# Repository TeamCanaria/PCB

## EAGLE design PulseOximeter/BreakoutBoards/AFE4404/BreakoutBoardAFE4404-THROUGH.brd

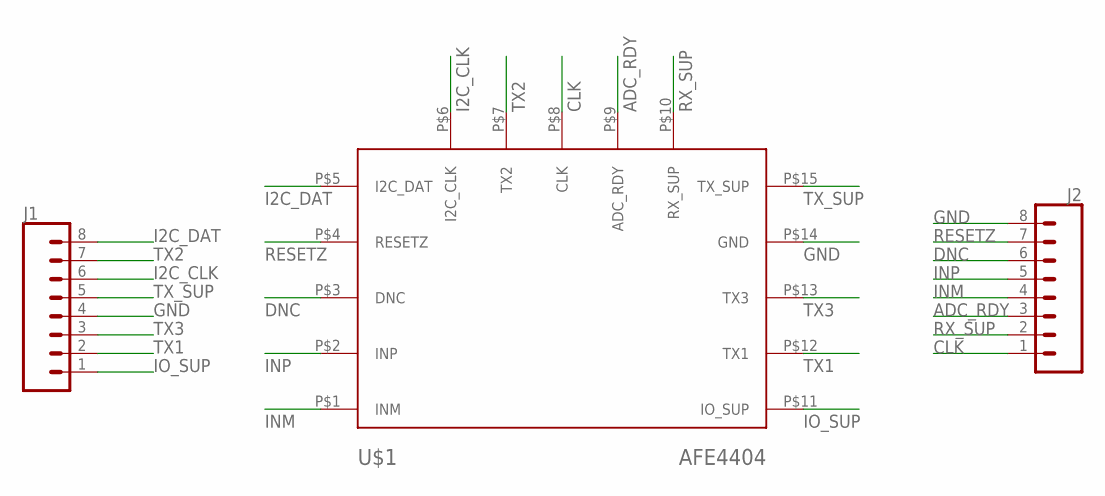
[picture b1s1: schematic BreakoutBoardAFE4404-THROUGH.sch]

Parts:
J1, J2: CONN_08"; 1X08
U$1: AFE4404; AFE4404-THROUGH

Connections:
ADC_RDY: J2.3, U$1.P$9 (ADC_RDY)
CLK: J2.1, U$1.P$8 (CLK)
DNC: J2.6, U$1.P$3 (DNC)
GND: J1.4, J2.8, U$1.P$14 (GND)
I2C_CLK: J1.6, U$1.P$6 (I2C_CLK)
I2C_DAT: J1.8, U$1.P$5 (I2C_DAT)
INM: J2.4, U$1.P$1 (INM)
INP: J2.5, U$1.P$2 (INP)
IO_SUP: J1.1, U$1.P$11 (IO_SUP)
RESETZ: J2.7, U$1.P$4 (RESETZ)
RX_SUP: J2.2, U$1.P$10 (RX_SUP)
TX1: J1.2, U$1.P$12 (TX1)
TX2: J1.7, U$1.P$7 (TX2)
TX3: J1.3, U$1.P$13 (TX3)
TX_SUP: J1.5, U$1.P$15 (TX_SUP)

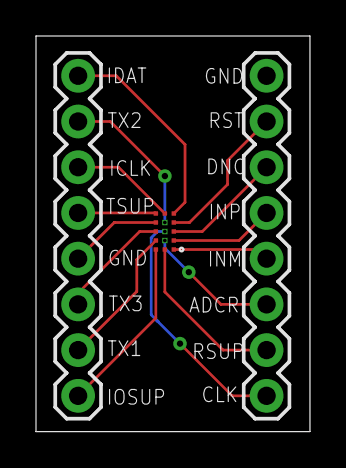
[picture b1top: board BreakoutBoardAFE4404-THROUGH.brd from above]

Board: 2 copper layers, 15.2 x 22.0 mm, 3 parts (0 on the bottom side), 15 nets.

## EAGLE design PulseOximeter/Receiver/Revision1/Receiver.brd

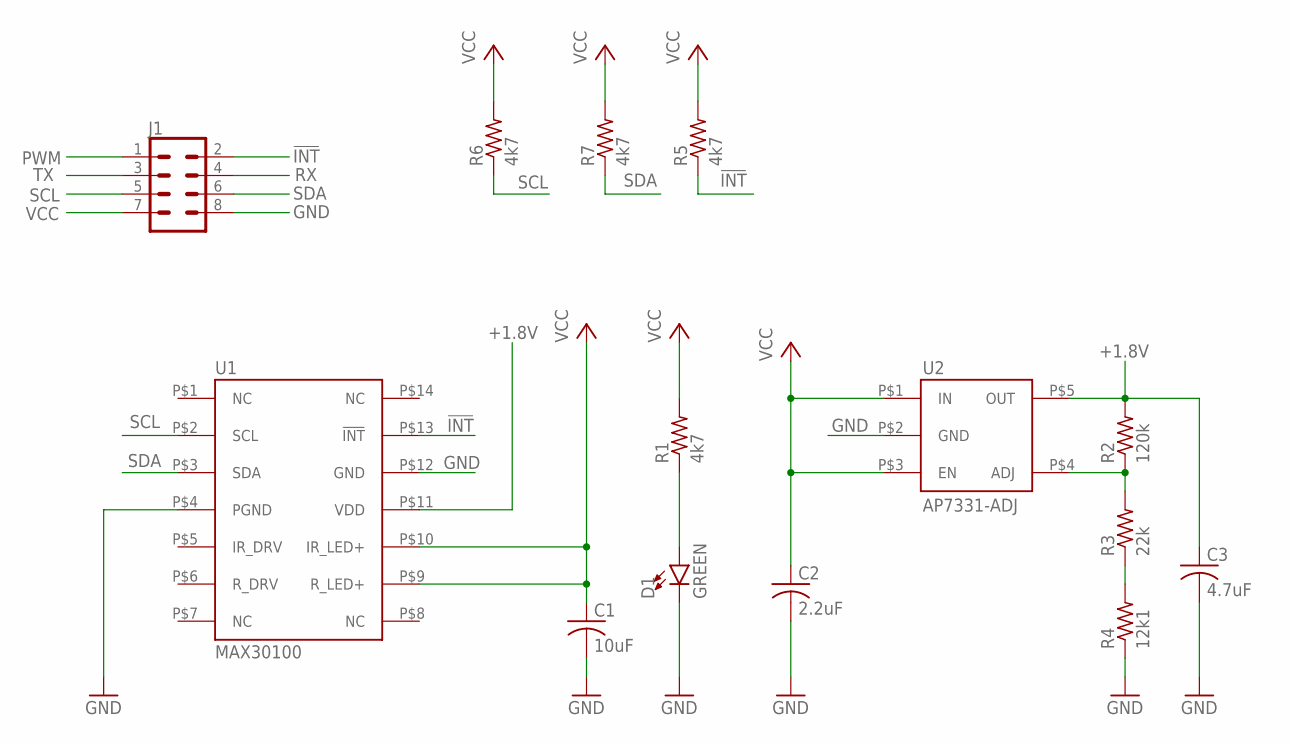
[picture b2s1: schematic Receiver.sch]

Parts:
C1: 10uF; C0805
C2: 2.2uF; C0805
C3: 4.7uF; C0805
D1: GREEN; LED-0603
J1: CONN_04X2; 2X4
R1, R5, R6, R7: 4k7; R0805
R2: 120k; R0805
R3: 22k; R0805
R4: 12k1; R0805
U1: MAX30100; 14OESIP
U2: AP7331-ADJ; SOT25

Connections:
!INT!: J1.2, R5.1, U1.P$13 (!INT!)
+1.8V: C3.1, R2.2, U1.P$11 (VDD), U2.P$5 (OUT)
GND: C1.2, C2.2, C3.2, D1.C, J1.8, R4.1, U1.P$4 (PGND), U1.P$12 (GND), U2.P$2 (GND)
unnamed: D1.A, R1.1
unnamed: R2.1, R3.2, U2.P$4 (ADJ)
unnamed: R3.1, R4.2
PWM: J1.1
RX: J1.4
SCL: J1.5, R6.1, U1.P$2 (SCL)
SDA: J1.6, R7.1, U1.P$3 (SDA)
TX: J1.3
VCC: C1.1, C2.1, J1.7, R1.2, R5.2, R6.2, R7.2, U1.P$9 (R_LED+), U1.P$10 (IR_LED+), U2.P$1 (IN), U2.P$3 (EN)

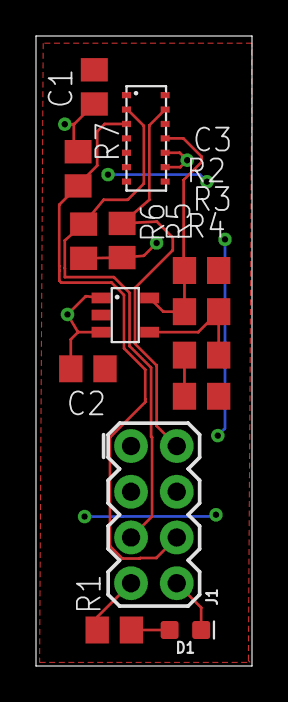
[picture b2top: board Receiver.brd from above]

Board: 2 copper layers, 12.0 x 35.0 mm, 14 parts (0 on the bottom side), 9 nets.

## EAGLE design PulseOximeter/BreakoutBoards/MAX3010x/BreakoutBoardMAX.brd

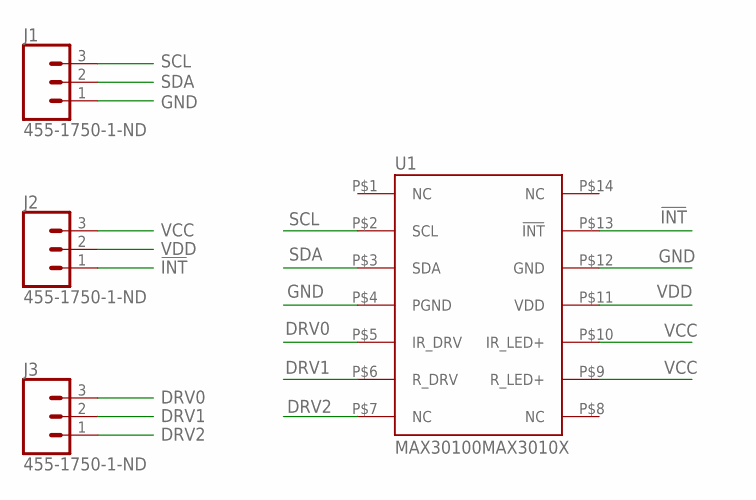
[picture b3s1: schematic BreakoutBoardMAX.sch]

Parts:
J1, J2, J3: 455-1750-1-ND; 1X03
U1: MAX30100MAX3010X; MAX_VERSATILE

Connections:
!INT!: J2.1, U1.P$13 (!INT!)
DRV0: J3.3, U1.P$5 (IR_DRV)
DRV1: J3.2, U1.P$6 (R_DRV)
DRV2: J3.1, U1.P$7 (NC)
GND: J1.1, U1.P$4 (PGND), U1.P$12 (GND)
SCL: J1.3, U1.P$2 (SCL)
SDA: J1.2, U1.P$3 (SDA)
VCC: J2.3, U1.P$9 (R_LED+), U1.P$10 (IR_LED+)
VDD: J2.2, U1.P$11 (VDD)

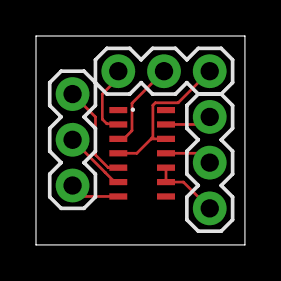
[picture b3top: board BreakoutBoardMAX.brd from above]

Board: 2 copper layers, 11.6 x 11.6 mm, 4 parts (0 on the bottom side), 9 nets.

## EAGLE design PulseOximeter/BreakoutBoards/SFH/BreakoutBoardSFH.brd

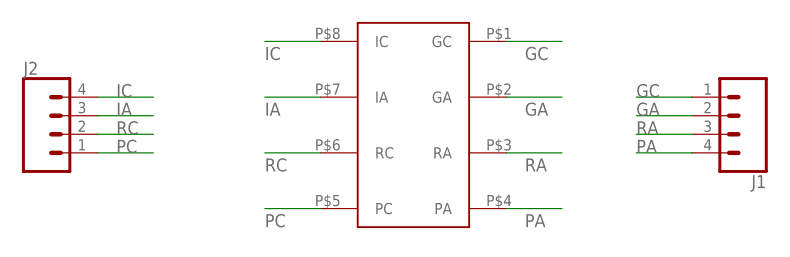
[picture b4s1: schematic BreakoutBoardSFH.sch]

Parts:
J1, J2: CONN_04; 1X04
U1: SFH7050

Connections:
GA: J1.2, U1.P$2 (GA)
GC: J1.1, U1.P$1 (GC)
IA: J2.3, U1.P$7 (IA)
IC: J2.4, U1.P$8 (IC)
PA: J1.4, U1.P$4 (PA)
PC: J2.1, U1.P$5 (PC)
RA: J1.3, U1.P$3 (RA)
RC: J2.2, U1.P$6 (RC)

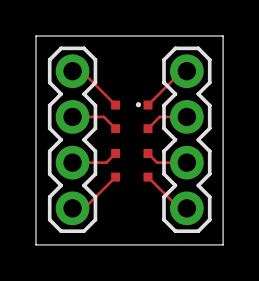
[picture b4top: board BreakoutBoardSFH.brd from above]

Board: 2 copper layers, 10.4 x 11.6 mm, 3 parts (0 on the bottom side), 8 nets.

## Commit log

2018-01-22 Updated AFE Breakout
    AFE submitted was incorrectly labelled and has now been corrected in files. The corrected pinout of submitted PCBs is included.

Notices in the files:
parts and their libraries:
SparkFun-Connectors: Licensing: Creative Commons ShareAlike 4.0 International - https://creativecommons.org/licenses/by-sa/4.0
